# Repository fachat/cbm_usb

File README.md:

# cbm_usb
USB solution for the Commodore Userport

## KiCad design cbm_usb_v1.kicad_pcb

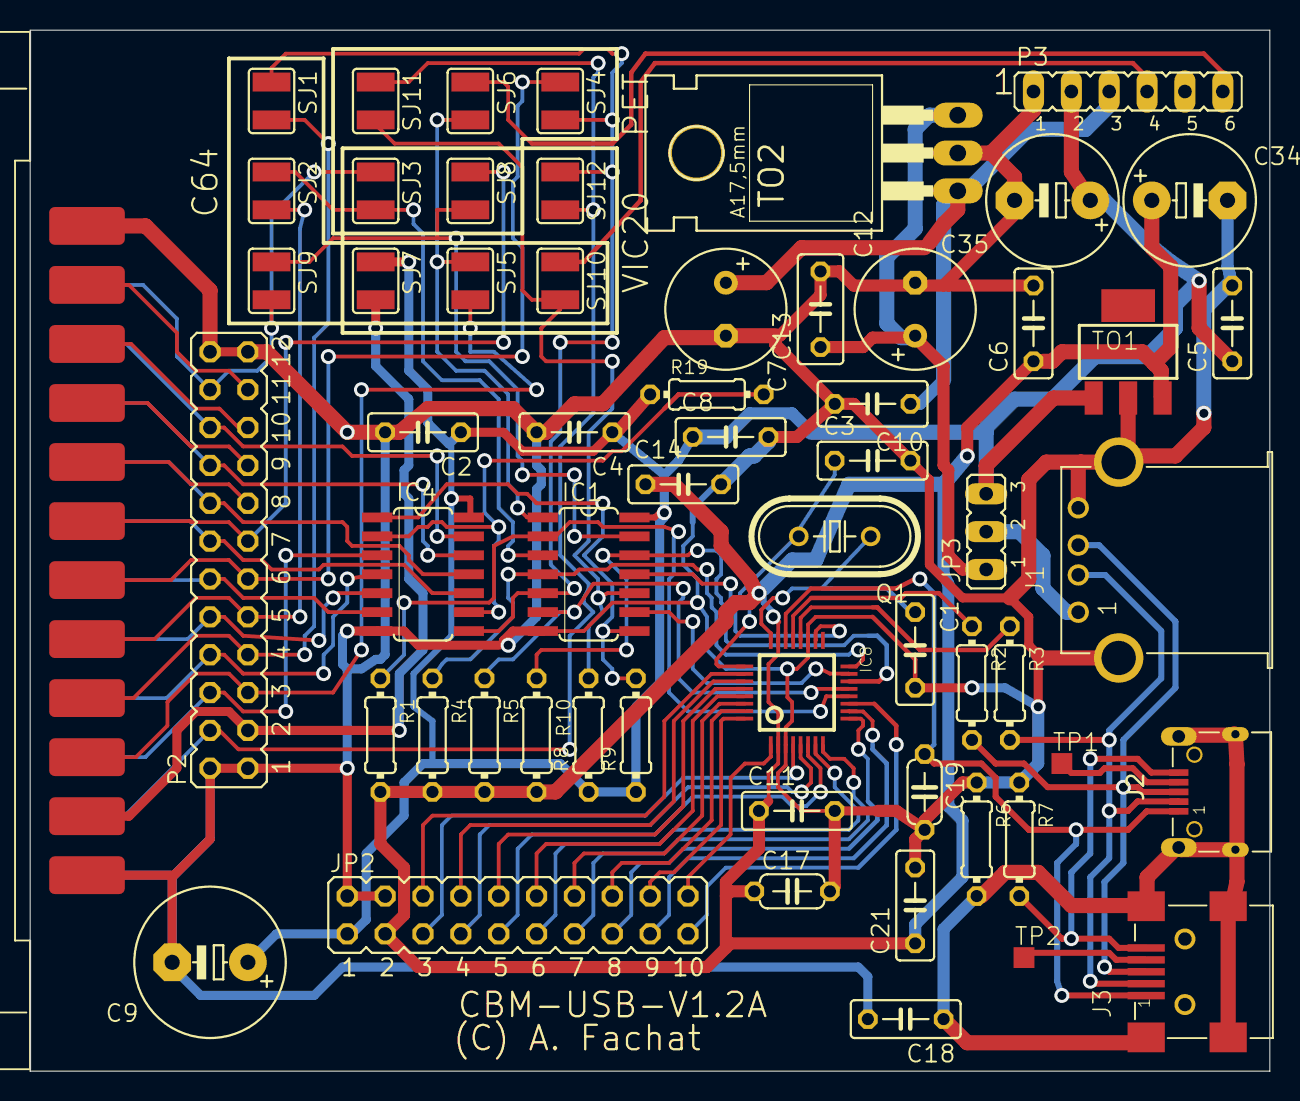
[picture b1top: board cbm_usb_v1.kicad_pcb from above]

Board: 2 copper layers, 83.2 x 69.8 mm, 59 parts (0 on the bottom side), 68 nets.

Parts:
C1, C3: 18p; C050-025X075
C2, C4, C5, C6, C8, C11: 100n; C050-025X075
C7, C12: 47u; E3,5-8
C9: >=10u; E5-10,5
C10, C13: 100n; C050-030X075
C14, C18, C21: 0.1u; C050-025X075
C17, C19: 1.0u Cer; C050-024X044
C34: >=10u; E5-8,5
C35: 1u; E5-8,5
CN1: USERPORT-C64-CONN; UPS24CONN
IC1: 74LS07; SO14
IC4: 74LS164D; SO14
IC8: MAX3421E; TQFP32-5MM
J1: 614004190021
J2: 629105150521
J3: 65100516121
JP2: IOPORT; JP10Q
JP3: JP2
P2: PETUSERPORT; FLAT24
P3: CBMTAPE; JP6
Q1: 12MHz; HC49U70
R1, R4, R5, R8, R9, R10: 3k3; 0204_7
R2, R3, R7: 33; 0204_7
R6: 10M; 0204_7
R19: 10k; 0204_7
SJ1, SJ2, SJ3, SJ4, SJ5, SJ6, SJ7, SJ8, SJ9, SJ10, SJ11, SJ12: SJW
TO1: LM2937SOT-3.3V; SOT223
TO2: LM2937-5V; TO220H
TP1, TP2: TPSQTP14SQ; TP14SQ

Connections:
3.3V: C6.1, C11.1, C14.1, C17.1, C21.1, C34.+, IC8.2, IC8.23, JP2.3, R1.2, R4.2, R5.2, R10.2, TO1.3
12MHZ: C1.1, IC8.24, Q1.1
/C64RES: CN1.3, P2.3, SJ5.2
/INT2: IC1.11, IC8.18
/PETINT/VICCLK: CN1.B, P2.B, SJ11.1, SJ12.2
/PETVICSEL: CN1.7, P2.7, SJ8.1
/RES: IC1.2, IC8.12, R1.1
/SPIINT: IC1.10, R8.2, SJ10.2, SJ11.2
/SPIRES: IC1.1, SJ5.1, SJ6.2
/SPISEL: IC1.13, SJ8.2, SJ9.1
/SS2: IC1.12, IC8.14, R10.1
C64CLK: CN1.4, P2.4, SJ1.2
C64DATA: CN1.5, P2.5, SJ2.2
D+: J1.3, J2.3, J3.3, R2.2
D-: J1.2, J2.2, J3.2, R3.2
GND: C1.2, C2.2, C3.2, C4.2, C5.2, C6.2, C7.-, C8.2, C9.-, C10.2, C11.2, C12.-, C13.2, C14.2, C17.2, C18.2, C19.2, C21.2, C34.-, C35.-, CN1.1, CN1.12, CN1.A, CN1.N, IC1.7, IC4.7, IC8.3, IC8.19, J1.4, J1.SHELL, J1.SHELL1, JP2.2, JP2.4, P2.1, P2.12, P2.A, P2.N, P3.1, R6.1, R7.1, TO1.2, TO2.C
GPIN0: IC8.26, JP2.6
GPIN1: IC8.27, JP2.8
GPIN2: IC8.28, JP2.10
GPIN3: IC8.29, JP2.12
GPIN4: IC8.30, JP2.14
GPIN5: IC8.31, JP2.16
GPIN6: IC8.32, JP2.18
GPIN7: IC8.1, JP2.20
GPOUT0: IC8.4, JP2.5
GPOUT1: IC8.5, JP2.7
GPOUT2: IC8.6, JP2.9
GPOUT3: IC8.7, JP2.11
GPOUT4: IC8.8, JP2.13
GPOUT5: IC8.9, JP2.15
GPOUT6: IC8.10, JP2.17
GPOUT7: IC8.11, JP2.19
IND0: CN1.C, IC4.3, P2.C
IND1: CN1.D, IC4.4, P2.D
IND2: CN1.E, IC4.5, P2.E
IND3: CN1.F, IC4.6, P2.F
IND4: CN1.H, IC4.10, P2.H
IND5: CN1.J, IC4.11, P2.J
IND6: CN1.K, IC4.12, P2.K
IND7: CN1.L, IC4.13, P2.L
MISO2: IC1.9, IC8.15
MOSI: IC1.4, IC8.16, R4.1
MOTOR: C7.+, C10.1, P3.3, TO2.B
unnamed: CN1.10, P2.10
unnamed: CN1.11, P2.11
unnamed: IC8.20, R3.1
unnamed: IC8.21, R2.1
unnamed: CN1.2, P2.2, SJ7.2
unnamed: CN1.8, P2.8
unnamed: CN1.9, P2.9
unnamed: C12.+, C13.1, JP3.1, TO2.E
unnamed: C3.1, IC8.25, Q1.2
unnamed: J2.4, TP1.TP
unnamed: J3.4, TP2.TP
unnamed: IC4.2, IC4.9, R19.2
PETCLK: CN1.6, P2.6, SJ4.1
PETVICDATA/C64SEL: CN1.M, P2.M, SJ3.1, SJ9.2
SCLK: IC1.6, IC8.13, R5.1
SHIELD: C18.1, J2.SHELL, J2.SHELL1, J2.SHELL2, J2.SHELL3, J3.SHELL, J3.SHELL1, J3.SHELL2, J3.SHELL3, R6.2
SPICLK: IC1.5, IC4.8, SJ1.1, SJ4.2, SJ12.1
SPIMISO: IC1.8, IC4.1, R9.2
SPIMOSI: IC1.3, SJ2.1, SJ3.2
TAPEREAD: P3.4, SJ10.1
TAPESENSE: P3.6, SJ6.1
USB5VOUT: J1.1, JP3.2
USBGND: J2.5, J3.5, R7.2
VBCOMP: C19.1, IC8.22, J2.1, J3.1
VCC: C2.1, C4.1, C5.1, C8.1, C9.+, C35.+, IC1.14, IC4.14, JP2.1, JP3.3, P3.2, R8.1, R9.1, R19.1, SJ7.1, TO1.1
